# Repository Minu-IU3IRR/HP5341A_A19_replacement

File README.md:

# HP5341A_A19_replacement

A project for restoring old HP5341A frequency counters.

this repo contains the Arduino sketch that enables full control over the intrument, even via Serial port usign standard VISA commands. if you wish to use the Arduno mega you will find the kicad project for the shield that allows easy connection of the wires on the mainboard and socket for the original display.
if you wish to use another board make shure that 5v can be handeled, all the logic on the instrument is 5V.

supported commands:
*IDN?    ->   standard ICSP command

:FREQ?   ->   last valid reading or zero.

:BAND?   ->   witch IF band the istrument is operating on.

:RES?    ->   the current resolution setted on the counter, expressed as the esponent of 10, example 2 => 10^2 Hz.

:DEAD?   ->   returns 1 if the instrument is in deadtime from gating, else retruns 0.

:GATE?   ->   returns 1 if the GATE is open, else returns false.

:STAT?   ->   returns a string representing the status of the instrument in human readable form to bedug.

-VERY IMPORTANT!
if you supply power to the arduino with the shield make shure to disconnect the 5V positive wire from the USB port so you will not connect your computer's 5V bus to the insturment one, BAD things can occur. the ground wire must remain connected. to supply the arduino from your PC just avoid soldering the +5V pins on the shield and the voltages are separated, keep in mind that the instrument must supply the display if original, it can pull up to 1A that the arduno or PC can not provide.

Feel free to reproduce all the content, just make shure to link this repo as the source!

under any circumstance i will take ANY responsability for damage of any kind to anything or anyone from reproducing any part of the cntents of this repo.....

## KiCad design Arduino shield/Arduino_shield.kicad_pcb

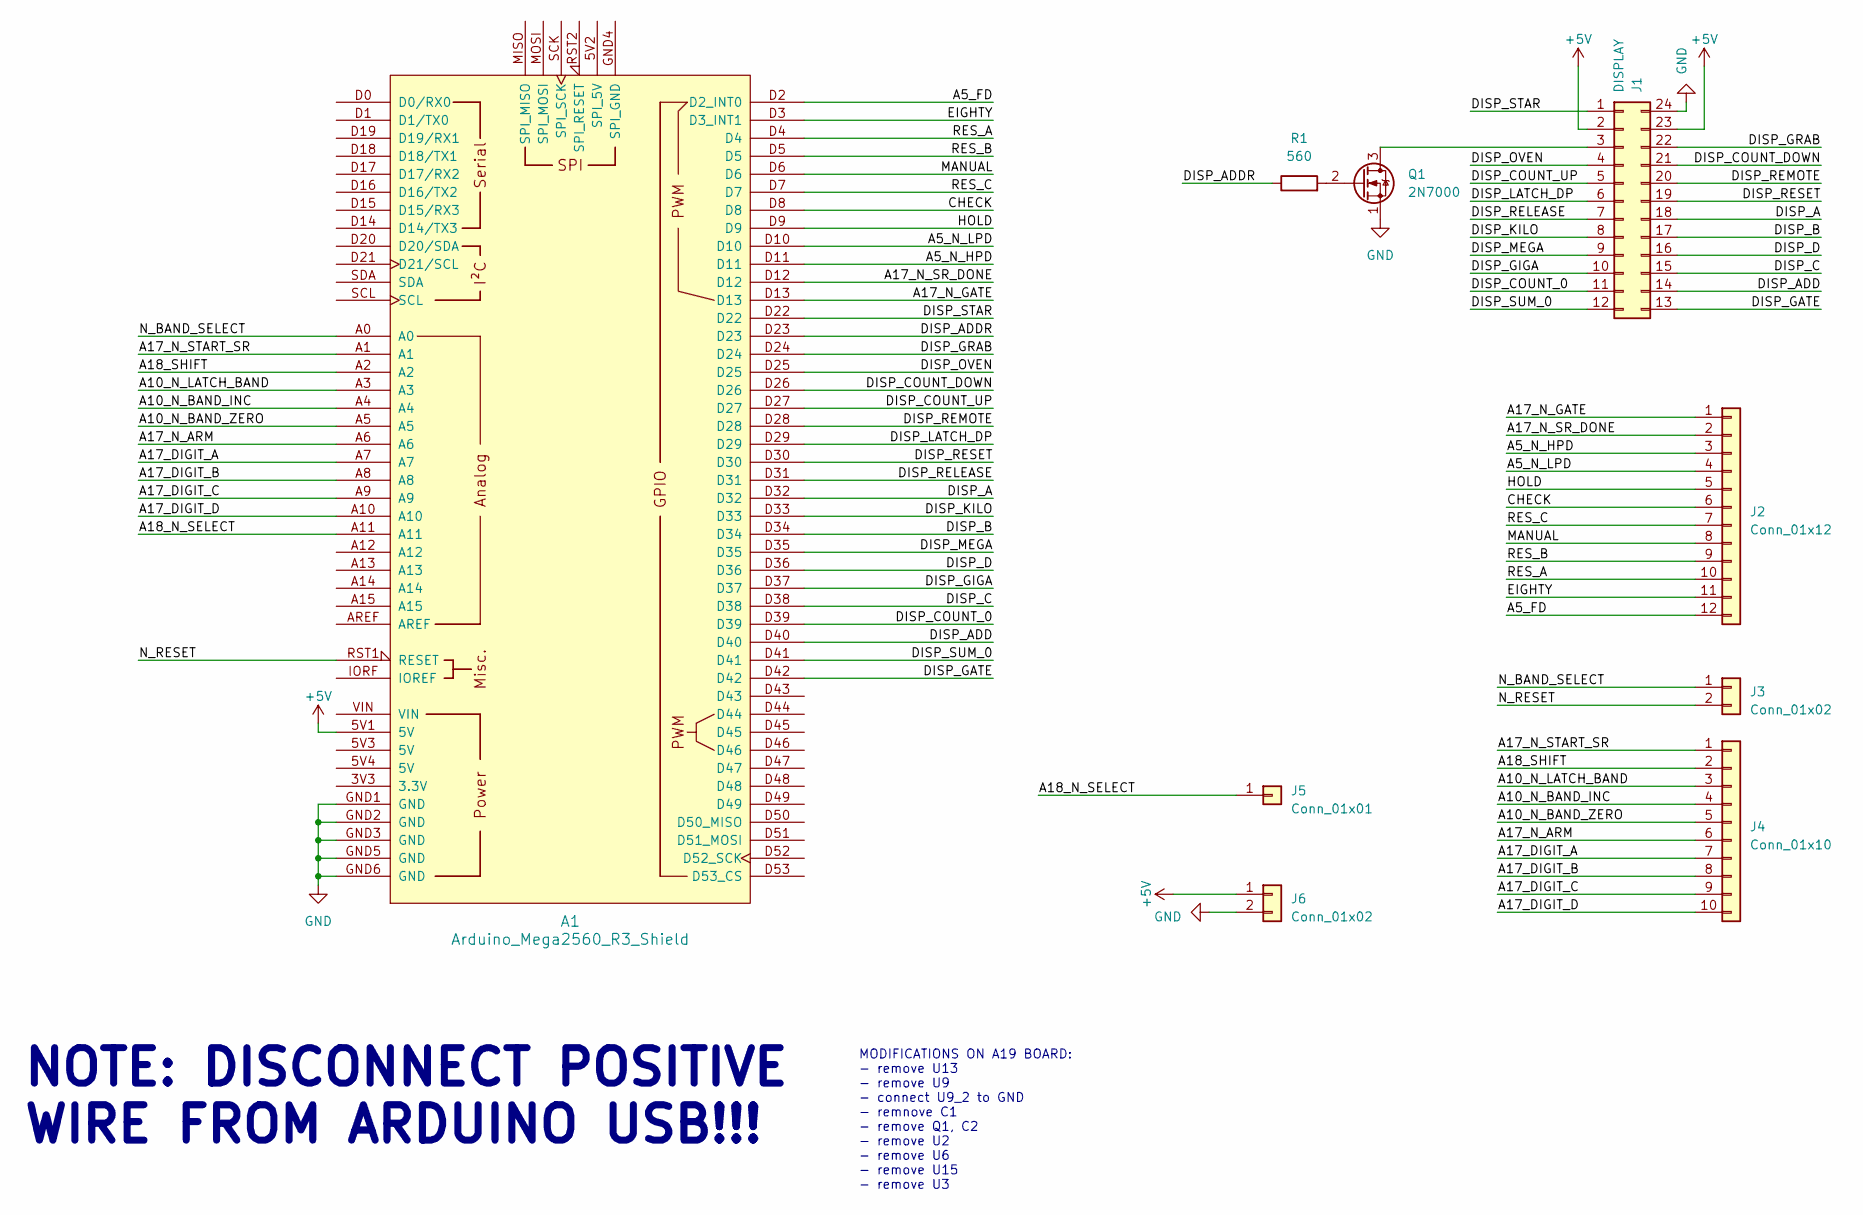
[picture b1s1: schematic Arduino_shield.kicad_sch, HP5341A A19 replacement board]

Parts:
A1: Arduino_Mega2560_R3_Shield
J1: DISPLAY; DIP-24_W15.24mm_Socket
J2: Conn_01x12; PinHeader_1x12_P2.54mm_Vertical
J3, J6: Conn_01x02; PinHeader_1x02_P2.54mm_Vertical
J4: Conn_01x10; PinHeader_1x10_P2.54mm_Vertical
J5: Conn_01x01; PinHeader_1x01_P2.54mm_Vertical
Q1: 2N7000; TO-92_Inline
R1: 560; R_Axial_DIN0207_L6.3mm_D2.5mm_P10.16mm_Horizontal

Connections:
+5V: A1.5V1 (5V), J1.2, J1.23, J6.1
/A5_FD: A1.D2 (D2_INT0), J2.12
/A5_N_HPD: A1.D11, J2.3
/A5_N_LPD: A1.D10, J2.4
/A10_N_BAND_INC: A1.A4, J4.4
/A10_N_BAND_ZERO: A1.A5, J4.5
/A10_N_LATCH_BAND: A1.A3, J4.3
/A17_DIGIT_A: A1.A7, J4.7
/A17_DIGIT_B: A1.A8, J4.8
/A17_DIGIT_C: A1.A9, J4.9
/A17_DIGIT_D: A1.A10, J4.10
/A17_N_ARM: A1.A6, J4.6
/A17_N_GATE: A1.D13, J2.1
/A17_N_SR_DONE: A1.D12, J2.2
/A17_N_START_SR: A1.A1, J4.1
/A18_N_SELECT: A1.A11, J5.1
/A18_SHIFT: A1.A2, J4.2
/CHECK: A1.D8, J2.6
/DISP_A: A1.D32, J1.18
/DISP_ADD: A1.D40, J1.14
/DISP_ADDR: A1.D23, R1.1
/DISP_B: A1.D34, J1.17
/DISP_C: A1.D38, J1.15
/DISP_COUNT_0: A1.D39, J1.11
/DISP_COUNT_DOWN: A1.D26, J1.21
/DISP_COUNT_UP: A1.D27, J1.5
/DISP_D: A1.D36, J1.16
/DISP_GATE: A1.D42, J1.13
/DISP_GIGA: A1.D37, J1.10
/DISP_GRAB: A1.D24, J1.22
/DISP_KILO: A1.D33, J1.8
/DISP_LATCH_DP: A1.D29, J1.6
/DISP_MEGA: A1.D35, J1.9
/DISP_OVEN: A1.D25, J1.4
/DISP_RELEASE: A1.D31, J1.7
/DISP_REMOTE: A1.D28, J1.20
/DISP_RESET: A1.D30, J1.19
/DISP_STAR: A1.D22, J1.1
/DISP_SUM_0: A1.D41, J1.12
/EIGHTY: A1.D3 (D3_INT1), J2.11
/HOLD: A1.D9, J2.5
/MANUAL: A1.D6, J2.8
/N_BAND_SELECT: A1.A0, J3.1
/N_RESET: A1.RST1 (RESET), J3.2
/RES_A: A1.D4, J2.10
/RES_B: A1.D5, J2.9
/RES_C: A1.D7, J2.7
GND: A1.GND1 (GND), A1.GND2 (GND), A1.GND3 (GND), A1.GND5 (GND), A1.GND6 (GND), J1.24, J6.2, Q1.1 (S)
unnamed: J1.3, Q1.3 (D)
unnamed: Q1.2 (G), R1.2

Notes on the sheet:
MODIFICATIONS ON A19 BOARD: - remove U13 - remove U9 - connect U9_2 to GND - remnove C1 - remove Q1, C2 - remove U2 - remove U6 - remove U15 - remove U3
NOTE: DISCONNECT POSITIVE WIRE FROM ARDUINO USB!!!

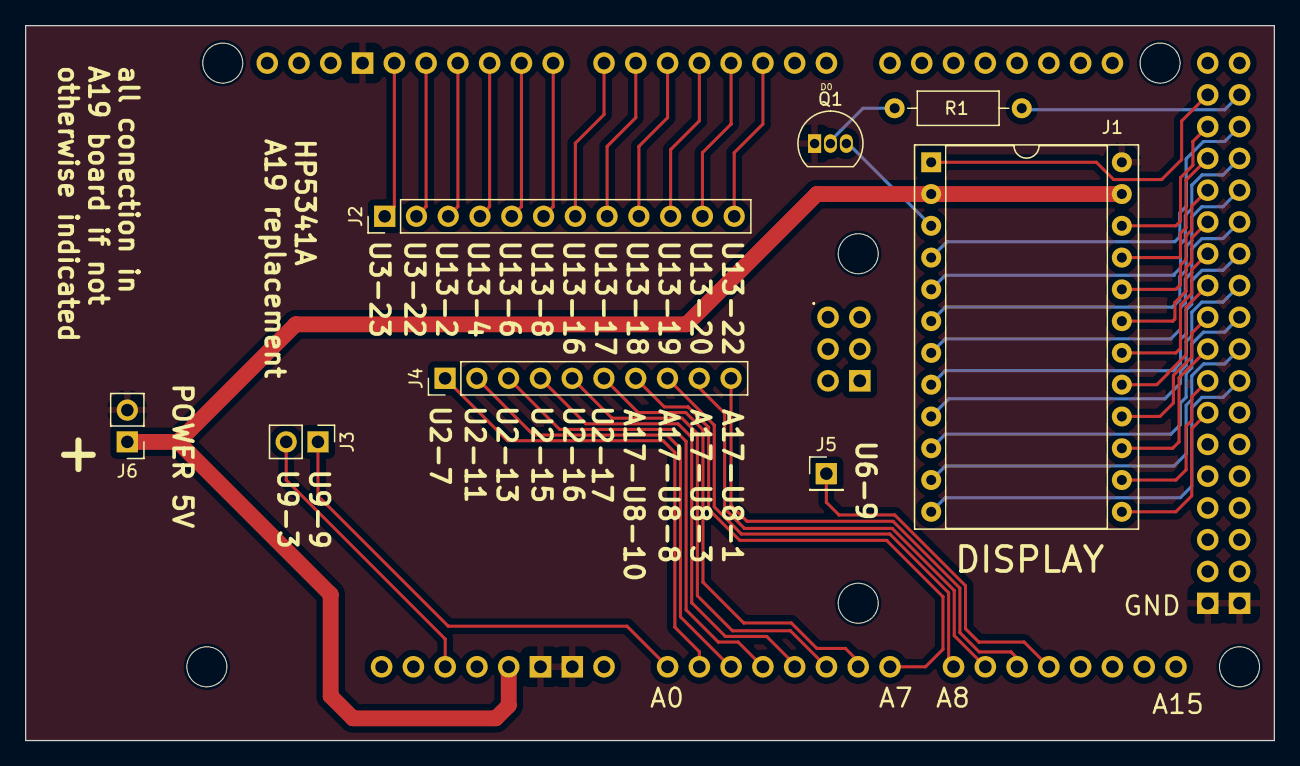
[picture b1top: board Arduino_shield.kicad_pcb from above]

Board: 2 copper layers, 99.8 x 57.1 mm, 9 parts (0 on the bottom side), 50 nets.

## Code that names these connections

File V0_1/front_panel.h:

#include <Arduino.h>

class BoardA19 {
private:
  int pin_MANUAL = 6;
  int pin_N_BAND_SELECT = A0;
  int pin_EIGHTY = 3;  // front panel selection, auto signal souting in hardware
  int pin_CHECK = 8;   // self test position
  int pin_RES_A = 4;
  int pin_RES_B = 5;
  int pin_RES_C = 7;

public:
  BoardA19();
  void init();
  bool band_automatic();
  bool band_button_pressed();
  bool input_high_range();
  bool input_check();
  int resolution();
};

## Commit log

2023-09-22 Add files via upload
    first commit
2023-09-26 Update V0_1.ino
    bug fix in decimal point position
